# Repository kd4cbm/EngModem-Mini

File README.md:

# EngModem Mini

A retro dial-up-modem-styled ESP32-S3 board: RS-232 (true DCE levels via
MAX3237), a 24x2 character VFD status display, a microSD card slot, 8
status LEDs, and USB-C, built around the ESP32-S3-WROOM-1U module. Runs
[Zimodem](https://github.com/BoZimmerman/Zimodem) - Bo Zimmerman's Hayes
AT-command modem emulator/internet gateway - via the
[Zimodem-VFD](https://github.com/kd4cbm/Zimodem-VFD) fork, which adds the
VFD status display this board uses. The firmware qualified on this exact
hardware, further specialised for it, is included in [`firmware/`](firmware/).

## Status: Rev5 built and functionally qualified

One Rev5 board has been built, brought up and bench-qualified with the firmware
in [`firmware/`](firmware/) (revision `firmware-v7-rev1`), September 2026:
programming over USB, boot and debug UART, WiFi, microSD, the VFD, the status
LEDs, RS-232 at every rate from 300 to 921600 baud, RTS/CTS flow control, DTR,
DCD and RI, and byte-exact data integrity through TCP connections. The full
results - and, just as importantly, **what was not tested** (no rail-voltage or
signal-level measurements, single unit, no long soak, no ESD/EMC) - are in
[`docs/QUALIFICATION.md`](docs/QUALIFICATION.md).

Bring-up turned up a few things worth knowing **before you build one**:

- **J12's pin order does not match most ready-made header-to-DE-9 cables** and
  the board will appear dead with one - see [`docs/J12_CABLE_GUIDE.md`](docs/J12_CABLE_GUIDE.md).
- **Three MAX3237 jumpers (J4/J5/J8) must be fitted** - see the jumper table in
  [`docs/BRING_UP.md`](docs/BRING_UP.md#3-set-the-jumpers).
- U3/U5 are hand-soldered and U5 was substituted - see [`docs/ERRATA.md`](docs/ERRATA.md).
- **Most front-panel LEDs read inverted on boards with the original U4.** MR, TR, SD, RD and CD go
  through U4, originally a non-inverting buffer, from active-low signals, so they were lit when they
  should be dark. The firmware corrects OH, AA and HS; replacing U4 with a pin-compatible inverting
  part (a TI CD74HCT640M) fixes the rest and has been **built and verified on hardware** -
  see [`docs/ERRATA.md`](docs/ERRATA.md#e11-most-front-panel-leds-read-inverted).
  Also **check the LED order at assembly** (two LEDs were swapped on the tested unit).
- The design-stage "all pins match the firmware" check missed signal direction and LED
  polarity; nine firmware and design issues were found and eight fixed in firmware during
  qualification (the LED inversion of five LEDs needs a hardware change) - see
  [`docs/ERRATA.md`](docs/ERRATA.md#e3-earlier-pin-cross-check-missed-signal-direction) and
  [`docs/QUALIFICATION.md`](docs/QUALIFICATION.md).
- **Use RTS/CTS for long transfers.** With flow control off, a long full-speed two-way stream
  can still lose data (the receive-buffer bug behind most of that is fixed in firmware v6b) -
  see [`docs/ERRATA.md`](docs/ERRATA.md#e12-serial-receive-buffer-was-256-bytes-not-4096-fixed-in-firmware-v6b).

This is a functional qualification of a single unit, not a compliance test.
Expect further revisions.

## Special thanks

This board exists to run [Bo Zimmerman](http://www.zimmers.net)'s
[Zimodem](https://github.com/BoZimmerman/Zimodem) - the Hayes AT-command
modem emulator this whole project is built around. None of this would
have a reason to exist without that project. Thank you, Bo.

## Board overview

- ESP32-S3-WROOM-1U (external U.FL antenna), 16MB flash / 8MB octal PSRAM
- MAX3237-based RS-232 level shifting, wired as **DCE** (straight-through
  DE-9 cable to a PC/terminal) - full modem control set: TXD, RXD, RTS,
  CTS, DTR, DSR, DCD, RI
- Noritake CU24025ECPB-W1J 24x2 character VFD, direct 4-bit parallel
  drive (no I2C bridge)
- microSD card slot (Hirose DM3AT-SF-PEJM5), dedicated SPI pins
- 8 status LEDs, including 3 direct-GPIO-driven (AA/HS/OH)
- USB-C (native USB-Serial-JTAG)
- 2-layer PCB, routed with [Freerouting](https://github.com/freerouting/freerouting) 2.3.0

## Verification

**Design checks** - every revision was checked with KiCad's own tools before
being carried forward:

- **ERC**: 32/32 clean (no unsuppressed errors/warnings)
- **DRC**: 1 finding, a pre-existing benign silkscreen-overlap warning on
  U1; 0 unconnected nets
- **Footprint/schematic sync**: clean
- **Firmware/hardware cross-check (design stage)**: every GPIO the firmware
  references was traced against the schematic netlist pin-by-pin - 18/18
  matched **by GPIO number and net name**. That check did not compare signal
  *direction* and so missed a reversed RTS/CTS assignment, found later on the
  real board and fixed in the firmware; see
  [`docs/ERRATA.md`](docs/ERRATA.md#e3-earlier-pin-cross-check-missed-signal-direction).

**Hardware qualification** - a real Rev5 board, tested on the bench with the
included firmware: [`docs/QUALIFICATION.md`](docs/QUALIFICATION.md).

## Prerequisite libraries

This project uses two public third-party KiCad libraries that aren't
bundled here - install both via KiCad's **Plugin and Content Manager**
before opening the project:

- **Espressif KiCad libraries** (`com_github_espressif_kicad-libraries`) -
  ESP32-S3-WROOM-1U symbol/footprint
- **MAX3237** - U1's symbol/footprint

The project's one genuinely custom dependency, a small `RetroWiFiModem`
library providing the SOIC-20W bus-transceiver symbol/footprint used at U4
(both the original 74HCT245 and the CD74HCT640M it was replaced with share
the symbol's underlying pinout), is bundled under
[`hardware/kicad/libraries/`](hardware/kicad/libraries/) and wired up via
the project-local `sym-lib-table`/`fp-lib-table`, so it
resolves automatically - no separate install needed for that one.

## RS-232 (J12) - DE-9 female, DCE pinout

DCE pinout in the **AT/Everex header order** (header pin *n* = DE-9 pin *n*) -
wire straight-through to a DTE (PC/terminal). **Many ready-made header-to-DE-9
cables use a different (DTK/Intel) order and will not work** - read
[`docs/J12_CABLE_GUIDE.md`](docs/J12_CABLE_GUIDE.md):

| Pin | 1 | 2 | 3 | 4 | 5 | 6 | 7 | 8 | 9 |
|---|---|---|---|---|---|---|---|---|---|
| Signal | DCD | RXD | TXD | DTR | GND | DSR | RTS | CTS | RI |

Full connector/power-regulation detail (including the U3/U5 substitution
below) is in [`PIN_MAP.md`](PIN_MAP.md); a running changelog is in
[`CHANGES.md`](CHANGES.md).

## Files

- [`firmware/`](firmware/) - the qualified firmware: source, prebuilt
  binaries with checksums, and the hardware QA test scripts (start with its
  [README](firmware/README.md))
- [`docs/`](docs/) - [`BRING_UP.md`](docs/BRING_UP.md) (builder's guide:
  jumpers, first power, flashing, troubleshooting),
  [`QUALIFICATION.md`](docs/QUALIFICATION.md) (test report),
  [`ERRATA.md`](docs/ERRATA.md) (known issues),
  [`J12_CABLE_GUIDE.md`](docs/J12_CABLE_GUIDE.md) (cabling)
- [`hardware/kicad/`](hardware/kicad/) - full KiCad 10 project (schematic
  + PCB), current as of **Rev5**
- [`hardware/kicad/libraries/`](hardware/kicad/libraries/) - bundled
  custom library (see [Prerequisite libraries](#prerequisite-libraries))
- [`enclosure/`](enclosure/) - Hammond 1455U2201BK panel drill/router jigs
  (front: VFD window, LEDs, mounting holes; rear: DB9, USB-C, power
  jack/switch, boot/reset, external antenna) - see its own
  [README](enclosure/README.md) for the preliminary-hardware disclaimer
  and usage instructions
- [`manufacturing/Gerbers_EngModem-Mini_Rev5.zip`](manufacturing/Gerbers_EngModem-Mini_Rev5.zip) -
  Gerber + Excellon drill files, ready to upload to a fab
- [`manufacturing/BOM_PCBA_JLCPCB.csv`](manufacturing/BOM_PCBA_JLCPCB.csv) -
  bill of materials for the SMD parts JLCPCB will assemble, with LCSC part
  numbers verified against LCSC's own listings where a specific
  manufacturer part is called for. Common passives (resistors, most
  capacitors) intentionally list full specs with no pinned LCSC number -
  JLCPCB's basic-parts catalog is a live, dynamic search that isn't
  reliably scriptable, and these are common enough values that matching
  one at checkout takes seconds. **U3, U4 and U5 are intentionally excluded**
  - see below.
- [`manufacturing/BOM_full.csv`](manufacturing/BOM_full.csv) - every part
  on the board, including the through-hole connectors, headers, LED
  positions, and U3/U5, for your own hand-assembly shopping list
- [`manufacturing/CPL_SMD.csv`](manufacturing/CPL_SMD.csv) - placement
  (component position) file for the JLCPCB-assembled SMD parts, in
  JLCPCB's expected column format (`Designator, Mid X, Mid Y, Layer,
  Rotation`), generated directly from the PCB's real component
  coordinates. U3, U4 and U5 excluded, same as the PCBA BOM.

Gerbers + BOM_PCBA_JLCPCB + CPL_SMD together are what JLCPCB's PCBA
(assembly) order flow asks for. **Before ordering, check every SMD part's
orientation and position in JLCPCB's assembly preview tool** - their
preview renders whichever specific LCSC library part it matched to each
BOM row, using that part's own reference point, which doesn't always
agree with KiCad's footprint origin (for angle *or* position). Their
preview UI lets you nudge/rotate a part and save the correction directly,
no file regeneration needed - do that check first, especially for U1
(MAX3237EIPWR) and U2 (the ESP32 module).

### U3 and U5 - excluded from PCBA, hand-solder these

JLCPCB's placement preview surfaced a real footprint mismatch on both
regulators: the originally spec'd parts (HGSEMI LM7805S2/TR for U3, ST
LD1086D2T33TR for U5) don't reliably match this board's 3-lead D2PAK/
TO-263-3 footprint - LCSC's own listings show both as 2-lead packages
(and JLCPCB's 3D model for U3 shows "TO263-5" case marking), while ST's
LD1086 datasheet itself defines two different D²PAK mechanical variants
under one ambiguous order code. Rather than risk a bad PCBA placement,
both are DNP for JLCPCB assembly - `BOM_full.csv` lists verified
replacement parts to hand-solder instead, sourced from Mouser/DigiKey:

- **U3**: onsemi **MC7805CD2TR4G** (D2PAK-3, CASE 936) - confirmed via
  onsemi's own MC7800 datasheet: Pin 1=Input, Pin 2=Ground=Tab, Pin
  3=Output, an exact match to this footprint and the schematic.
- **U5**: TI **LM1086CSX-3.3/NOPB** (DDPAK/TO-263, package KTT; the
  qualified board uses the in-stock **LM1086IS-3.3/NOPB**, same package and
  pinout, industrial temp grade) -
  confirmed via TI's own datasheet: Pin 1=ADJ/GND, Pin 2+Tab=Output, Pin
  3=Input, an exact match to this footprint and the schematic (tab wired
  to Output by design).

### U4 - excluded from PCBA, hand-solder this

Unlike U3/U5, this wasn't a footprint mismatch - the schematic's generic 74HCT245 (non-inverting)
placed and worked fine, but reads five front-panel LEDs inverted (see
[`docs/ERRATA.md`](docs/ERRATA.md#e11-most-front-panel-leds-read-inverted)). The fix is a
pin/package-compatible **inverting** part, TI **CD74HCT640M** (SOIC-20-300mil, same footprint) - hand-swapped
on the qualified unit and verified correct (2026-09-29; a pad was pulled during desoldering and needed a
trace/pad-level repair, worth planning for). LCSC **C1548168** - 0 units in LCSC's own direct stock at
last check, ~3,000 available through LCSC's Other Suppliers channel at a 9-18 business day lead time
(checked 2026-09-29, re-verify before ordering) - excluded here pending confirmed assembly-line stock.
Must be the **HCT** variant, not HC (HC doesn't meet the 3.3V input threshold at 5V).

## Revision history

| Rev | Notes |
|---|---|
| 0-1 | Original modular layout and placement baseline |
| 2 | SD card socket swapped from a pin header to the real microSD socket (Hirose DM3AT-SF-PEJM5); full reroute |
| 3 | Second SD placement experiment; full reroute; 69 net-derived pin-function silkscreen labels added across every header/LED footprint |
| 4 | Dedicated 0.5mm net class for `/DC-IN`; solid (non-thermal-relief) zone connections on regulator/shield GND tabs; local `/VCC` copper pour + thermal vias around U5; ESP32 power-filter components (L1/C11/C12) relocated for shorter real routed-copper paths to U2 |
| 5 | **Current** - via stitching added under U2's ground-pad cluster (9 vias, exposed copper + matching pads mirrored onto the bottom layer) for bottom-side hand-soldering access; keepout zone added around that cluster, full rip/reroute; U3/U5 excluded from PCBA per the footprint mismatch below |

## License

Hardware design files (schematic, PCB) are released under
[CERN-OHL-S v2](https://cern-ohl.web.cern.ch/) - a strongly-reciprocal
open hardware license: modifications to these design files must be
released under the same license if you distribute hardware built from
them. See [LICENSE](LICENSE).

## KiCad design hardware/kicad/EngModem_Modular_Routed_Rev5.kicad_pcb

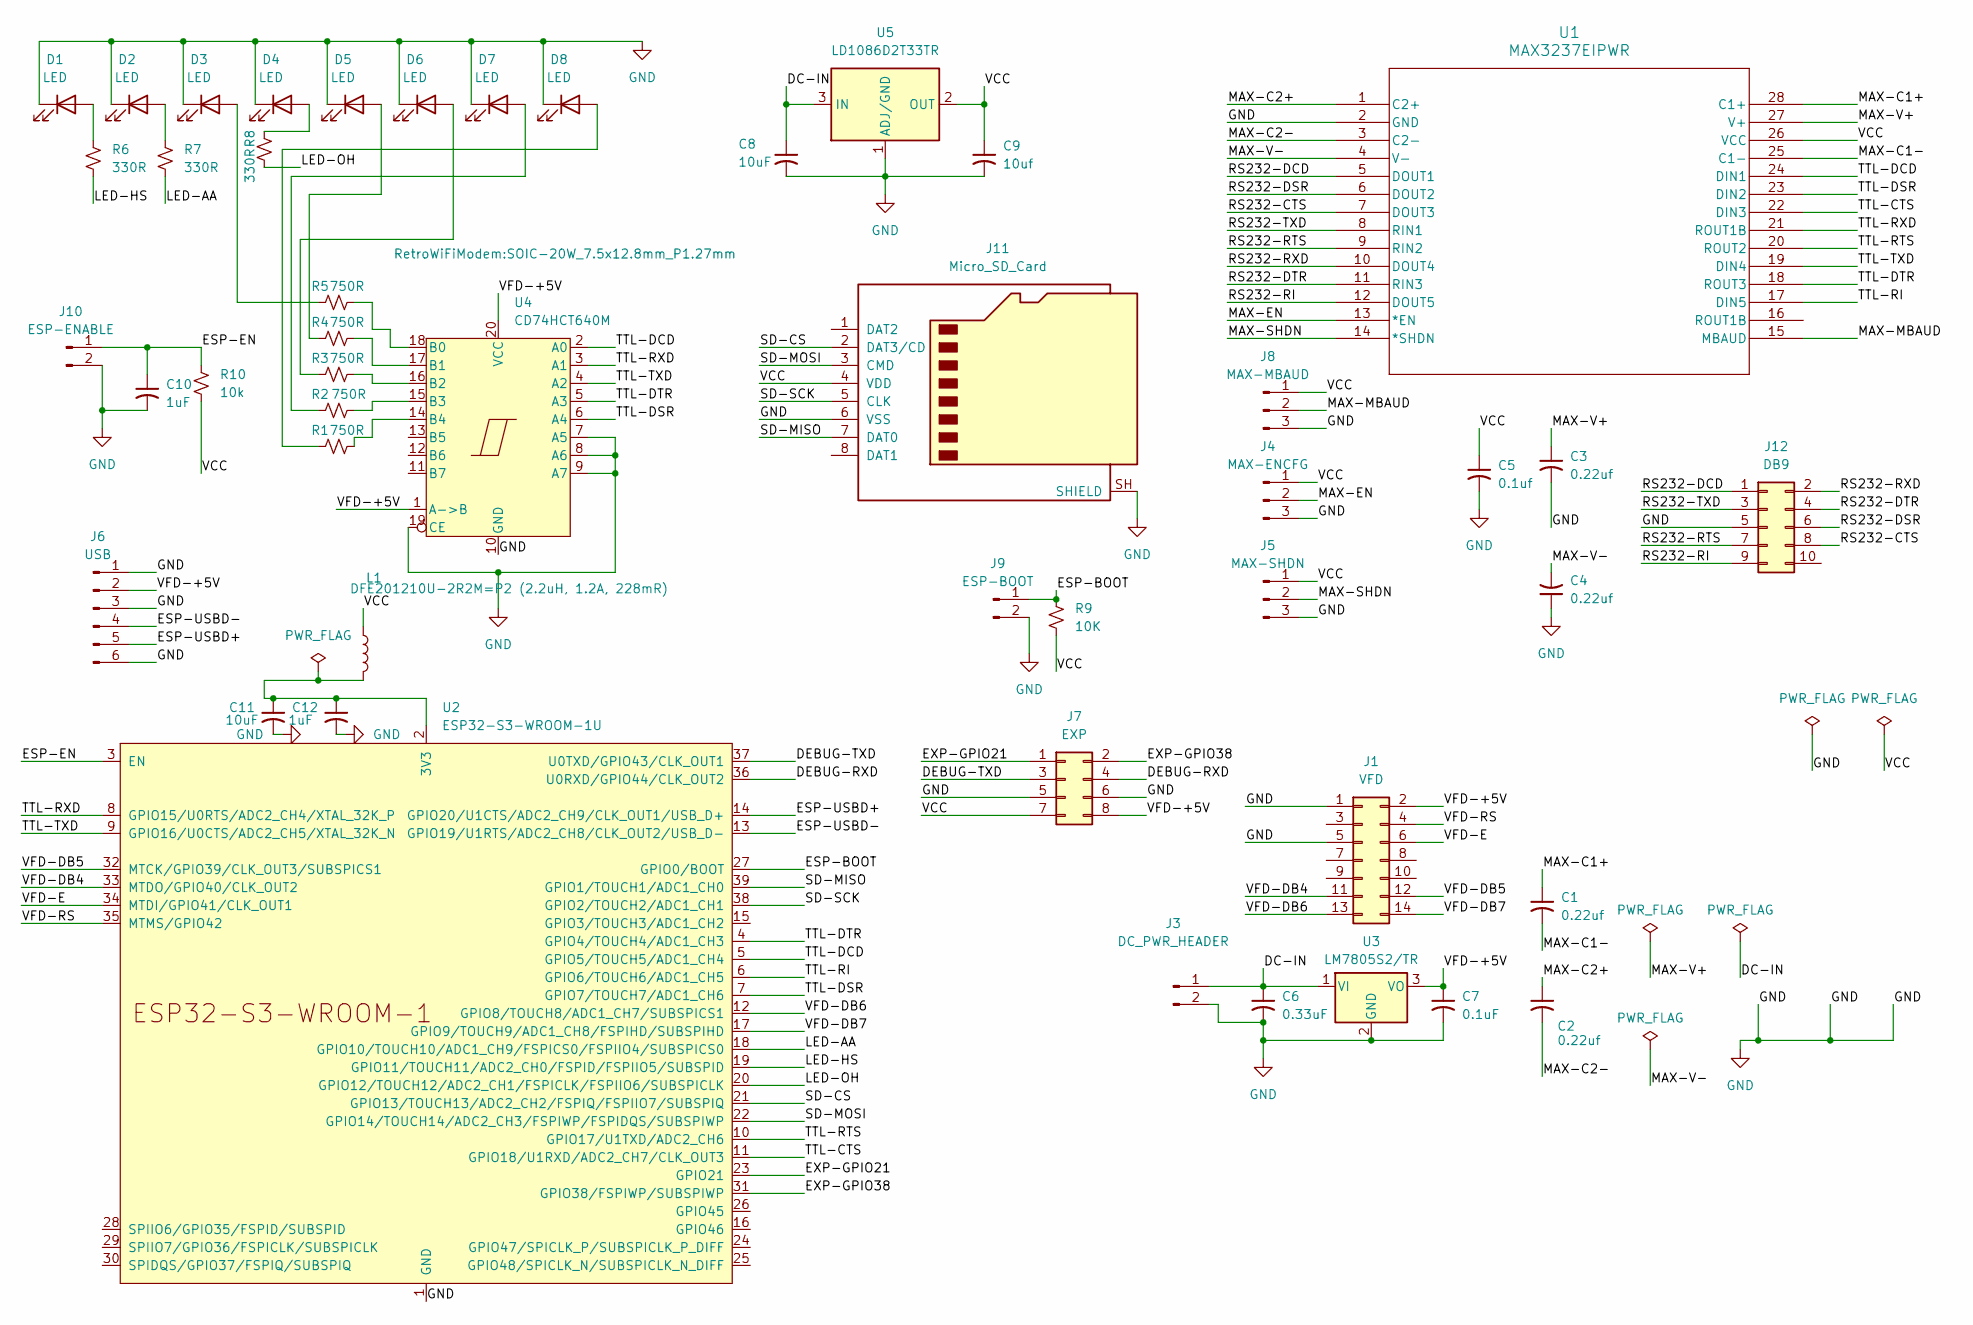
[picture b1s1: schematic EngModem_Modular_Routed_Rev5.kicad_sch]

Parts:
C1, C2, C3, C4: 0.22uf; C_0805_2012Metric
C5: 0.1uf; C_0805_2012Metric
C6: 0.33uF; C_0805_2012Metric
C7: 0.1uF; C_0805_2012Metric
C8: 10uF; C_1206_3216Metric
C9: 10uf; C_0805_2012Metric
C10, C12: 1uF; C_0805_2012Metric
C11: 10uF; C_0805_2012Metric
D1, D2, D3, D4, D5, D6, D7, D8: LED; PinHeader_1x02_P2.54mm_Vertical
J1: VFD; PinHeader_2x07_P2.54mm_Vertical
J3: DC_PWR_HEADER; PinHeader_1x02_P2.54mm_Vertical
J4: MAX-ENCFG; PinHeader_1x03_P2.54mm_Vertical
J5: MAX-SHDN; PinHeader_1x03_P2.54mm_Vertical
J6: USB; PinHeader_1x06_P2.54mm_Vertical
J7: EXP; PinHeader_2x04_P2.54mm_Vertical
J8: MAX-MBAUD; PinHeader_1x03_P2.54mm_Vertical
J9: ESP-BOOT; PinHeader_1x02_P2.54mm_Vertical
J10: ESP-ENABLE; PinHeader_1x02_P2.54mm_Vertical
J11: Micro_SD_Card; microSD_HC_Hirose_DM3AT-SF-PEJM5
J12: DB9; IDC-Header_2x05_P2.54mm_Vertical
L1: DFE201210U-2R2M=P2 (2.2uH, 1.2A, 228mR); L_0805_2012Metric
R1, R2, R3, R4, R5: 750R; R_0805_2012Metric
R6, R7, R8: 330R; R_0805_2012Metric
R9: 10K; R_0805_2012Metric
R10: 10k; R_0805_2012Metric
U1: MAX3237EIPWR; PW28
U2: ESP32-S3-WROOM-1U
U3: LM7805S2/TR; TO-263-3_TabPin2
U4: CD74HCT640M; SOIC-20W_7.5x12.8mm_P1.27mm
U5: LD1086D2T33TR; TO-263-3_TabPin2

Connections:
/DC-IN: C6.1, C8.1, J3.1, U3.1 (VI), U5.3 (IN)
/DEBUG-RXD: J7.4, U2.36 (U0RXD/GPIO44/CLK_OUT2)
/DEBUG-TXD: J7.3, U2.37 (U0TXD/GPIO43/CLK_OUT1)
/ESP-BOOT: J9.1, R9.1, U2.27 (GPIO0/BOOT)
/ESP-EN: C10.1, J10.1, R10.1, U2.3 (EN)
/ESP-USBD+: J6.5, U2.14 (GPIO20/U1CTS/ADC2_CH9/CLK_OUT1/USB_D+)
/ESP-USBD-: J6.4, U2.13 (GPIO19/U1RTS/ADC2_CH8/CLK_OUT2/USB_D-)
/EXP-GPIO21: J7.1, U2.23 (GPIO21)
/EXP-GPIO38: J7.2, U2.31 (GPIO38/FSPIWP/SUBSPIWP)
/LED-AA: R7.2, U2.18 (GPIO10/TOUCH10/ADC1_CH9/FSPICS0/FSPIIO4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)
/LED-HS: R6.2, U2.19 (GPIO11/TOUCH11/ADC2_CH0/FSPID/FSPIIO5/S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)
/LED-OH: R8.2, U2.20 (GPIO12/TOUCH12/ADC2_CH1/FSPICLK/FSPIIO6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)
/MAX-C1+: C1.1, U1.28 (C1+)
/MAX-C1-: C1.2, U1.25 (C1-)
/MAX-C2+: C2.1, U1.1 (C2+)
/MAX-C2-: C2.2, U1.3 (C2-)
/MAX-EN: J4.2, U1.13 (*EN)
/MAX-MBAUD: J8.2, U1.15 (MBAUD)
/MAX-SHDN: J5.2, U1.14 (*SHDN)
/MAX-V+: C3.1, U1.27 (V+)
/MAX-V-: C4.2, U1.4 (V-)
/RS232-CTS: J12.8, U1.7 (DOUT3)
/RS232-DCD: J12.1, U1.5 (DOUT1)
/RS232-DSR: J12.6, U1.6 (DOUT2)
/RS232-DTR: J12.4, U1.11 (RIN3)
/RS232-RI: J12.9, U1.12 (DOUT5)
/RS232-RTS: J12.7, U1.9 (RIN2)
/RS232-RXD: J12.2, U1.10 (DOUT4)
/RS232-TXD: J12.3, U1.8 (RIN1)
/SD-CS: J11.2 (DAT3/CD), U2.21 (GPIO13/TOUCH13/ADC2_CH2/FSPIQ/FSPIIO7/S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)
/SD-MISO: J11.7 (DAT0), U2.39 (GPIO1/TOUCH1/ADC1_CH0)
/SD-MOSI: J11.3 (CMD), U2.22 (GPIO14/TOUCH14/ADC2_CH3/FSPIWP/FSPIDQS/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)
/SD-SCK: J11.5 (CLK), U2.38 (GPIO2/TOUCH2/ADC1_CH1)
/TTL-CTS: U1.22 (DIN3), U2.11 (GPIO18/U1RXD/ADC2_CH7/CLK_OUT3)
/TTL-DCD: U1.24 (DIN1), U2.5 (GPIO5/TOUCH5/ADC1_CH4), U4.2 (A0)
/TTL-DSR: U1.23 (DIN2), U2.7 (GPIO7/TOUCH7/ADC1_CH6), U4.6 (A4)
/TTL-DTR: U1.18 (ROUT3), U2.4 (GPIO4/TOUCH4/ADC1_CH3), U4.5 (A3)
/TTL-RI: U1.17 (DIN5), U2.6 (GPIO6/TOUCH6/ADC1_CH5)
/TTL-RTS: U1.20 (ROUT2), U2.10 (GPIO17/U1TXD/ADC2_CH6)
/TTL-RXD: U1.21 (ROUT1B), U2.8 (GPIO15/U0RTS/ADC2_CH4/XTAL_32K_P), U4.3 (A1)
/TTL-TXD: U1.19 (DIN4), U2.9 (GPIO16/U0CTS/ADC2_CH5/XTAL_32K_N), U4.4 (A2)
/VCC: C5.1, C9.1, J4.1, J5.1, J7.7, J8.1, J11.4 (VDD), L1.1, R9.2, R10.2, U1.26 (VCC), U5.2 (OUT)
/VFD-+5V: C7.1, J1.2, J6.2, J7.8, U3.3 (VO), U4.1 (A->B), U4.20 (VCC)
/VFD-DB4: J1.11, U2.33 (MTDO/GPIO40/CLK_OUT2)
/VFD-DB5: J1.12, U2.32 (MTCK/GPIO39/CLK_OUT3/SUBSPICS1)
/VFD-DB6: J1.13, U2.12 (GPIO8/TOUCH8/ADC1_CH7/SUBSPICS1)
/VFD-DB7: J1.14, U2.17 (GPIO9/TOUCH9/ADC1_CH8/FSPIHD/SUBSPIHD)
/VFD-E: J1.6, U2.34 (MTDI/GPIO41/CLK_OUT1)
/VFD-RS: J1.4, U2.35 (MTMS/GPIO42)
GND: C3.2, C4.1, C5.2, C6.2, C7.2, C8.2, C9.2, C10.2, C11.2, C12.2, D1.1 (K), D2.1 (K), D3.1 (K), D4.1 (K), D5.1 (K), D6.1 (K), D7.1 (K), D8.1 (K), J1.1, J1.5, J3.2, J4.3, J5.3, J6.1, J6.3, J6.6, J7.5, J7.6, J8.3, J9.2, J10.2, J11.6 (VSS), J11.SH (SHIELD), J12.5, U1.2 (GND), U2.1 (GND), U2.40 (GND), U2.41 (GND), U3.2 (GND), U4.7 (A5), U4.8 (A6), U4.9 (A7), U4.10 (GND), U4.19 (CE), U5.1 (ADJ/GND)
unnamed: D1.2 (A), R6.1
unnamed: D2.2 (A), R7.1
unnamed: D3.2 (A), R5.2
unnamed: D4.2 (A), R8.1
unnamed: D5.2 (A), R4.2
unnamed: D6.2 (A), R3.2
unnamed: D7.2 (A), R2.2
unnamed: D8.2 (A), R1.2
unnamed: C11.1, C12.1, L1.2, U2.2 (3V3)
unnamed: R5.1, U4.18 (B0)
unnamed: R4.1, U4.17 (B1)
unnamed: R3.1, U4.16 (B2)
unnamed: R2.1, U4.15 (B3)
unnamed: R1.1, U4.14 (B4)

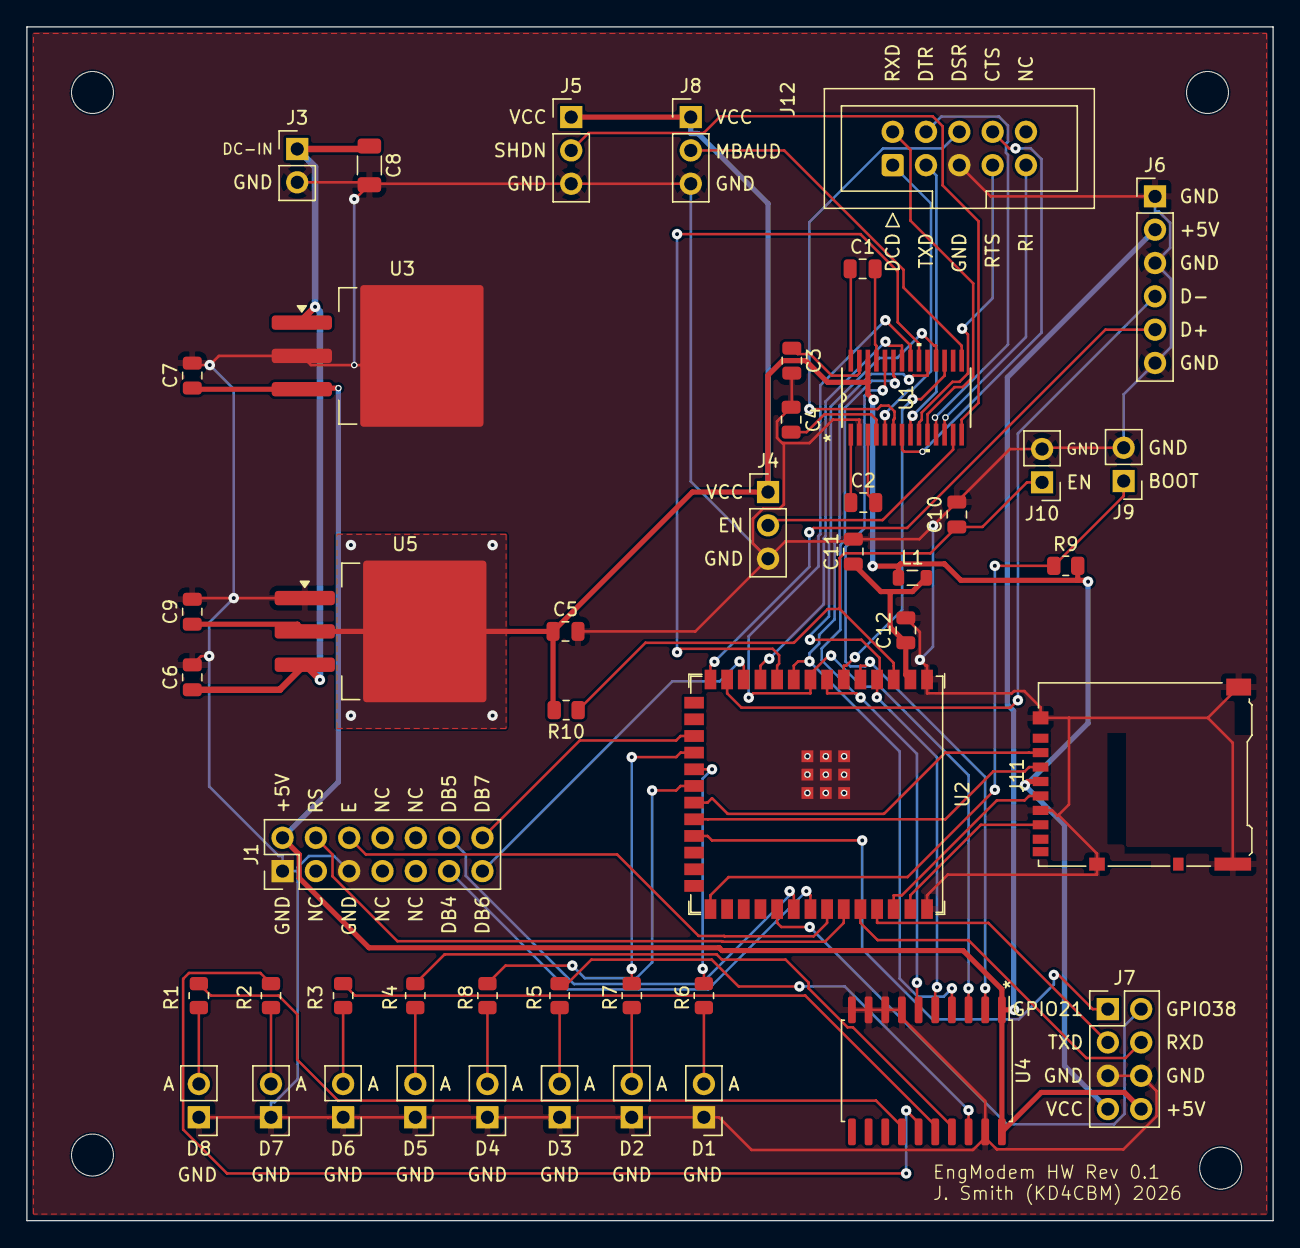
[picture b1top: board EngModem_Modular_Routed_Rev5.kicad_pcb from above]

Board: 2 copper layers, 95.0 x 91.0 mm, 51 parts (0 on the bottom side), 64 nets.

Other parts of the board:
MH1_TL, MH2_TR, MH3_BL, MH4_BR: MountingHole_3.2mm_M3

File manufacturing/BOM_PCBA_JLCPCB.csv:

Designator,Value,Package,Manufacturer,MPN,LCSC Part #,Notes
C1,0.22uF,0805,,,,"X7R ceramic, >=16V. Common value - match at JLCPCB checkout against their basic-parts catalog."
C2,0.22uF,0805,,,,"X7R ceramic, >=16V. Common value - match at JLCPCB checkout against their basic-parts catalog."
C3,0.22uF,0805,,,,"X7R ceramic, >=16V. Common value - match at JLCPCB checkout against their basic-parts catalog."
C4,0.22uF,0805,,,,"X7R ceramic, >=16V. Common value - match at JLCPCB checkout against their basic-parts catalog."
C5,0.1uF,0805,,,,"X7R ceramic, >=16V. VCC bypass. Common value - match at checkout."
C6,0.33uF,0805,,,,"X7R ceramic, >=16V. Common value - match at checkout."
C7,0.1uF,0805,,,,"X7R ceramic, >=16V. Common value - match at checkout."
C8,10uF,1206,,,,"X5R/X7R ceramic, >=16V. Common value - match at checkout."
C9,10uF,0805,,,,"X5R/X7R ceramic, >=16V. Common value - match at checkout."
C10,1uF,0805,,,,"X7R ceramic, >=16V. Common value - match at checkout."
C12,1uF,0805,,,,"X7R ceramic, >=16V. Common value - match at checkout."
C11,10uF,0805,,,,"X5R/X7R ceramic, >=16V. Common value - match at checkout."
L1,"2.2uH, 1.2A, 228mOhm, shielded",0805,Murata,DFE201210U-2R2M=P2,C2049745,"Verified exact MPN match, in stock (checked 2026-09-03)."
R1,750R,0805,,,,1%. Common value - match at checkout.
R2,750R,0805,,,,1%. Common value - match at checkout.
R3,750R,0805,,,,1%. Common value - match at checkout.
R4,750R,0805,,,,1%. Common value - match at checkout.
R5,750R,0805,,,,1%. Common value - match at checkout.
R6,330R,0805,,,,1%. Common value - match at checkout.
R7,330R,0805,,,,1%. Common value - match at checkout.
R8,330R,0805,,,,1%. Common value - match at checkout.
R9,10K,0805,,,,1%. Common value - match at checkout.
R10,10K,0805,,,,1%. Common value - match at checkout.
U1,MAX3237EIPWR,TSSOP-28,Texas Instruments,MAX3237EIPWR,C2671155,"Verified exact MPN match, in stock (checked 2026-09-03)."
U2,ESP32-S3-WROOM-1U-N16R8,SMD 18x19.2mm module,Espressif,ESP32-S3-WROOM-1U-N16R8,C3013946,"Verified exact MPN match, in stock (checked 2026-09-03)."
U4,74HCT245,SOIC-20W (300mil / 7.5x12.8mm),Nexperia,"74HCT245D,653",C5979,"Substituted manufacturer part (schematic value is generic) - same function and package, in stock (checked 2026-09-03)."
J11,Micro SD card socket,SMD push-push,Hirose,DM3AT-SF-PEJM5,C114218,"Verified exact MPN match, in stock (checked 2026-09-03). Suffix-specific reel variants also exist on LCSC (e.g. (11)/(21)/(40)/(41)) - electrically identical, differ only in packaging/reel."

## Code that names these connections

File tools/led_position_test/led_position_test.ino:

// EngModem Mini (Rev5) - front-panel LED polarity/position confirmation test
//
// Steps through the 8 LEDs in the order the DESIGN says they sit, left to right,
// lighting each one steadily for 3 seconds while the VFD shows:
//   row 1: "Pos N/8 D<designator>  ON/OFF"  (or the live pin level for hardware-driven slots)
//   row 2: the LED's label and function
// You watch which physical LED lights and compare it with the position/designator shown.
//
// LED wiring facts used here (from the Rev5 netlist; every LED lights when its
// drive signal is HIGH - anode -> resistor -> signal, cathode -> GND):
//   Direct GPIO : HS = GPIO11, AA = GPIO10, OH = GPIO12
//   Via U4 (now a CD74HCT640, inverting): the LED follows a TTL signal net
//     MR = /TTL-DSR  (GPIO7,  ESP output)  -> can be driven
//     SD = /TTL-TXD  (GPIO16, ESP output)  -> can be driven
//     CD = /TTL-DCD  (GPIO5,  ESP output)  -> can be driven
//     TR = /TTL-DTR  (GPIO4,  driven by the MAX3237 from the PC's DTR)  -> NOT driven
//     RD = /TTL-RXD  (GPIO15, driven by the MAX3237 from the PC's TXD)  -> NOT driven
// TR and RD nets are OUTPUTS of the MAX3237, so the ESP must not fight them: those
// two pins are left as inputs and their slots only show the live pin level, same as
// before the U4 swap - replacing U4 does not change which nets are ESP outputs vs
// MAX3237 outputs, only the polarity of the ones the ESP does drive.
//   - open a terminal on the modem COM port: TR (DTR) goes OFF
//   - type characters in it: RD flickers
//
// Runs forever (repeats after position 8). Touches nothing but GPIO and the VFD:
// no WiFi, no SPIFFS, no saved config. Reflash the normal firmware afterwards.

#include <Arduino.h>

// U4 (74HCT245) has been replaced with an inverting CD74HCT640: the LEDs that go through U4
// (MR, TR, SD, RD, CD) now light when the ESP32 pin is LOW. This is the first hardware
// confirmation of that swap - if MR/SD/CD light in the wrong sense here, the swap did not
// behave as the datasheet predicted.
#define U4_INVERTING 1

// --- VFD (same pins and init sequence as the real firmware, vfd.ino) ---
#define VFD_RS  42
#define VFD_E   41
#define VFD_DB4 40
#define VFD_DB5 39
#define VFD_DB6 8
#define VFD_DB7 9
#define VFD_COLS 24

static void vfdPulseEnable() {
  digitalWrite(VFD_E, HIGH); delayMicroseconds(1);
  digitalWrite(VFD_E, LOW);  delayMicroseconds(1);
}
static void vfdWriteNibble(uint8_t n) {
  digitalWrite(VFD_DB7, (n >> 3) & 1);
  digitalWrite(VFD_DB6, (n >> 2) & 1);
  digitalWrite(VFD_DB5, (n >> 1) & 1);
  digitalWrite(VFD_DB4, (n >> 0) & 1);
  vfdPulseEnable();
}
static void vfdWriteByte(uint8_t rs, uint8_t v) {
  digitalWrite(VFD_RS, rs ? HIGH : LOW);
  delayMicroseconds(1);
  vfdWriteNibble((v >> 4) & 0x0F);
  vfdWriteNibble(v & 0x0F);
  if (rs == 0 && v <= 0x03) delayMicroseconds(100); else delayMicroseconds(1);
}
static void vfdSequence() {          // the firmware's init, minus its 250 ms power-up wait
  vfdWriteNibble(0b0010);
  delayMicroseconds(100);
  vfdWriteByte(0, 0x20);             // Function set (4-bit)
  vfdWriteByte(0, 0x0C);             // Display on, cursor off
  vfdWriteByte(0, 0x06);             // Entry mode
  vfdWriteByte(0, 0x01);             // Clear
}
static void vfdRow(uint8_t row, const char *text) {   // writes exactly 24 columns, space-padded
  vfdWriteByte(0, row ? 0xC0 : 0x80);
  bool end = false;
  for (int i = 0; i < VFD_COLS; i++) {
    char c = end ? ' ' : text[i];
    if (c == 0) { end = true; c = ' '; }
    vfdWriteByte(1, (uint8_t)c);
  }
}

// --- LED table, in DESIGN position order (position 1 = leftmost) ---
enum Kind { DRIVEN, HW_INPUT };
struct Led {
  const char *row2;       // label + function, max 24 chars
  int pin;                // GPIO that makes the LED light when HIGH (or that we read)
  Kind kind;
  const char *sigName;    // shown for HW_INPUT slots
  bool viaU4;             // true if the LED is fed through U4 (affected by U4_INVERTING)
  const char *designator; // PCB silkscreen reference (D8..D1, left to right)
};
static const Led LEDS[8] = {
  { "MR - Modem Ready (DSR)",  7,  DRIVEN,   "",     true,  "D8" },
  { "TR - Term. Ready (DTR)",  4,  HW_INPUT, "DTR",  true,  "D7" },
  { "SD - Send Data (TXD)",    16, DRIVEN,   "",     true,  "D6" },
  { "RD - Recv Data (RXD)",    15, HW_INPUT, "RXD",  true,  "D5" },
  { "OH - Off Hook",           12, DRIVEN,   "",     false, "D4" },
  { "CD - Carrier Det (DCD)",  5,  DRIVEN,   "",     true,  "D3" },
  { "AA - Auto Answer",        10, DRIVEN,   "",     false, "D2" },
  { "HS - High Speed",         11, DRIVEN,   "",     false, "D1" },
};

#define SLOT_MS   3000UL      // steady-on duration per LED

// Light or darken a driven LED, allowing for the inverting U4 replacement.
static void drive(int idx, bool on) {
  bool level = on;
  if (LEDS[idx].viaU4 && U4_INVERTING) level = !level;
  digitalWrite(LEDS[idx].pin, level ? HIGH : LOW);
}

static void allDrivenOff() {
  for (int i = 0; i < 8; i++)
    if (LEDS[i].kind == DRIVEN) drive(i, false);
}

static void show(int idx, bool on) {
  char r1[VFD_COLS + 1];
  if (LEDS[idx].kind == DRIVEN)
    snprintf(r1, sizeof r1, "Pos %d/8 %s  %s", idx + 1, LEDS[idx].designator, on ? "ON " : "OFF");
  else
    snprintf(r1, sizeof r1, "Pos %d/8 %s  %s:%c", idx + 1, LEDS[idx].designator, LEDS[idx].sigName,
             digitalRead(LEDS[idx].pin) ? 'H' : 'L');
  vfdRow(0, r1);
  vfdRow(1, LEDS[idx].row2);
}

void setup() {
  Serial0.begin(115200);                       // debug UART on J7 (optional)

  // VFD pins
  const int vp[] = { VFD_RS, VFD_E, VFD_DB4, VFD_DB5, VFD_DB6, VFD_DB7 };
  for (int p : vp) pinMode(p, OUTPUT);
  digitalWrite(VFD_E, LOW); digitalWrite(VFD_RS, LOW);
  delay(250);
  vfdSequence();

  // LED drive pins (all are outputs in the normal firmware too)
  for (int i = 0; i < 8; i++)
    if (LEDS[i].kind == DRIVEN) { pinMode(LEDS[i].pin, OUTPUT); drive(i, false); }
  // MAX3237-driven nets: inputs only, never driven
  pinMode(4,  INPUT);   // /TTL-DTR
  pinMode(15, INPUT);   // /TTL-RXD
  // keep the other modem lines at their normal firmware idle levels
  pinMode(6,  OUTPUT); digitalWrite(6,  HIGH);   // RI inactive
  pinMode(18, OUTPUT); digitalWrite(18, LOW);    // RTS asserted (PC's CTS)
  pinMode(17, INPUT);                            // CTS-in (PC's RTS)

  Serial0.println("\r\nEngModem Mini LED polarity/position test - watch the front panel, left to right");
}

void loop() {
  vfdSequence();                               // re-send init each round in case the first was missed
  vfdRow(0, "LED polarity test"); vfdRow(1, "Watch left to right");
  allDrivenOff();
  delay(2000);

  for (int i = 0; i < 8; i++) {
    Serial0.printf("Position %d (%s): %s\r\n", i + 1, LEDS[i].designator, LEDS[i].row2);
    if (LEDS[i].kind == DRIVEN) drive(i, true);
    uint32_t start = millis();
    while (millis() - start < SLOT_MS) {
      show(i, true);                            // refreshed periodically (also recovers a lost write)
      delay(250);
    }
    allDrivenOff();
  }
  vfdRow(0, "Round complete"); vfdRow(1, "Repeating...");
  delay(1500);
}

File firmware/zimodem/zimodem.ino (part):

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// EngModem "Mini" custom PCB: reuses the ESP32-S3-16R8 DevKitC-1 pin map
// below (ARDUINO_ESP32S3_DEV block) since the wiring matches it exactly,
// but it is NOT that dev board - it has no onboard addressable RGB LED on
// GPIO38 (that pin is a general-purpose expansion header pin instead), and
// it has 3 direct-drive status LEDs on GPIO10/11/12 that the dev board
// doesn't have at all. Gates the two spots below where "any ESP32-S3-16R8
// DevKitC-1 build" and "this specific custom board" need different behavior.
#define ENGMODEM_MINI_BOARD true
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                                        repo root for the full rationale. */
#  define DEFAULT_PIN_DCD GPIO_NUM_5
# ifdef ENGMODEM_MINI_BOARD
   // RTS/CTS are wired DCE-style on the EngModem Mini PCB: GPIO17 is fed by the
   // MAX3237's ROUT2 (the PC's RTS, from DB9 pin 7) and GPIO18 drives DIN3 (out to
   // the PC's CTS, DB9 pin 8). Zimodem's UART flow control needs CTS as an INPUT and
   // RTS as an OUTPUT, so on this board those roles sit on the opposite GPIOs from
   // the dev-board layout in the #else branch. Without this swap the firmware
   // drives GPIO17 (which ROUT2 also drives) and reads a floating GPIO18.
#  define DEFAULT_PIN_CTS GPIO_NUM_17 // input: PC's RTS via MAX3237 ROUT2
#  define DEFAULT_PIN_RTS GPIO_NUM_18 // output: to PC's CTS via MAX3237 DIN3
# else
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#  define DEFAULT_PIN_RTS GPIO_NUM_17 // espdev cts pin
# endif
#  define DEFAULT_PIN_RI GPIO_NUM_6
#  define DEFAULT_PIN_DSR GPIO_NUM_7  // moved from GPIO9 to close the gap in the J1 run
#  define DEFAULT_PIN_SND -1
#  define DEFAULT_PIN_OTH -1 // pulse pin
#  define DEFAULT_PIN_DTR GPIO_NUM_4
#  define DEFAULT_PIN_TXD GPIO_NUM_16
#  define DEFAULT_PIN_RXD GPIO_NUM_15
#  define DEFAULT_PIN_SD_CS   GPIO_NUM_13 // moved from GPIO14 - GPIO14 is now SD MOSI
#  define DEFAULT_PIN_SD_MOSI GPIO_NUM_14
#  define DEFAULT_PIN_SD_MISO GPIO_NUM_1
#  define DEFAULT_PIN_SD_SCK  GPIO_NUM_2
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   // flash/PSRAM at its 1.8V domain, confirmed reserved in Espressif's own
   // docs. DB7 was there originally and caused a hard no-boot the moment it
   // was wired up; DB6 landed there in the last revision while fixing an
   // unrelated GPIO38/LED conflict, which was an equally bad landing spot
   // that just hadn't been wired up yet to fail visibly. Both now moved to
   // J1's GPIO8/GPIO9 (freed earlier when the VFD I2C bridge was removed) -
   // this means DB6/DB7 physically move to J1, separate from RS/E/DB4/DB5
   // on J3, since J3 has no remaining safe pins after this correction.
#  define DEFAULT_PIN_VFD_DB6 GPIO_NUM_8
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void setup()
{
#if defined(ARDUINO_ESP32S3_DEV) && !defined(ENGMODEM_MINI_BOARD)
  // This board's onboard addressable RGB LED is GPIO38 (Espressif DevKitC-1
  // v1.1 J3 header docs - not the same pin the Arduino core's generic
  // esp32s3 variant assumes for RGB_BUILTIN, which is why neopixelWrite()
  // is called with the literal pin number here instead of that constant).
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  // an addressable LED holds whatever it last received until a new frame
  // is clocked in, it doesn't reset itself just because the pin goes idle.
  // Skipped entirely on ENGMODEM_MINI_BOARD: that board has no RGB LED on
  // GPIO38 at all - it's a general expansion header pin there instead, and
  // this WS2812 protocol write would just be a spurious pulse train on it.
  neopixelWrite(38, 0, 0, 0);
#endif
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# ifdef ARDUINO_ESP32S3_DEV
  pinSupport[1]=true;
# ifdef ENGMODEM_MINI_BOARD
  // DTR is on GPIO4 on this board, which the dev-board list below skips. Without
  // this, pinMode(pinDTR,INPUT) is never called and the pin reads a constant level.
  pinSupport[4]=true;
# endif
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

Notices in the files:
firmware/zimodem/zimodem.ino:
Copyright 2016-2026 Bo Zimmerman
Licensed under the Apache License, Version 2.0 (the "License");
